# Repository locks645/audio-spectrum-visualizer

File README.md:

# audio-spectrum-visualizer

SDSU Senior Design 2024-2025, Team 14 Audio Spectrum Visualizer

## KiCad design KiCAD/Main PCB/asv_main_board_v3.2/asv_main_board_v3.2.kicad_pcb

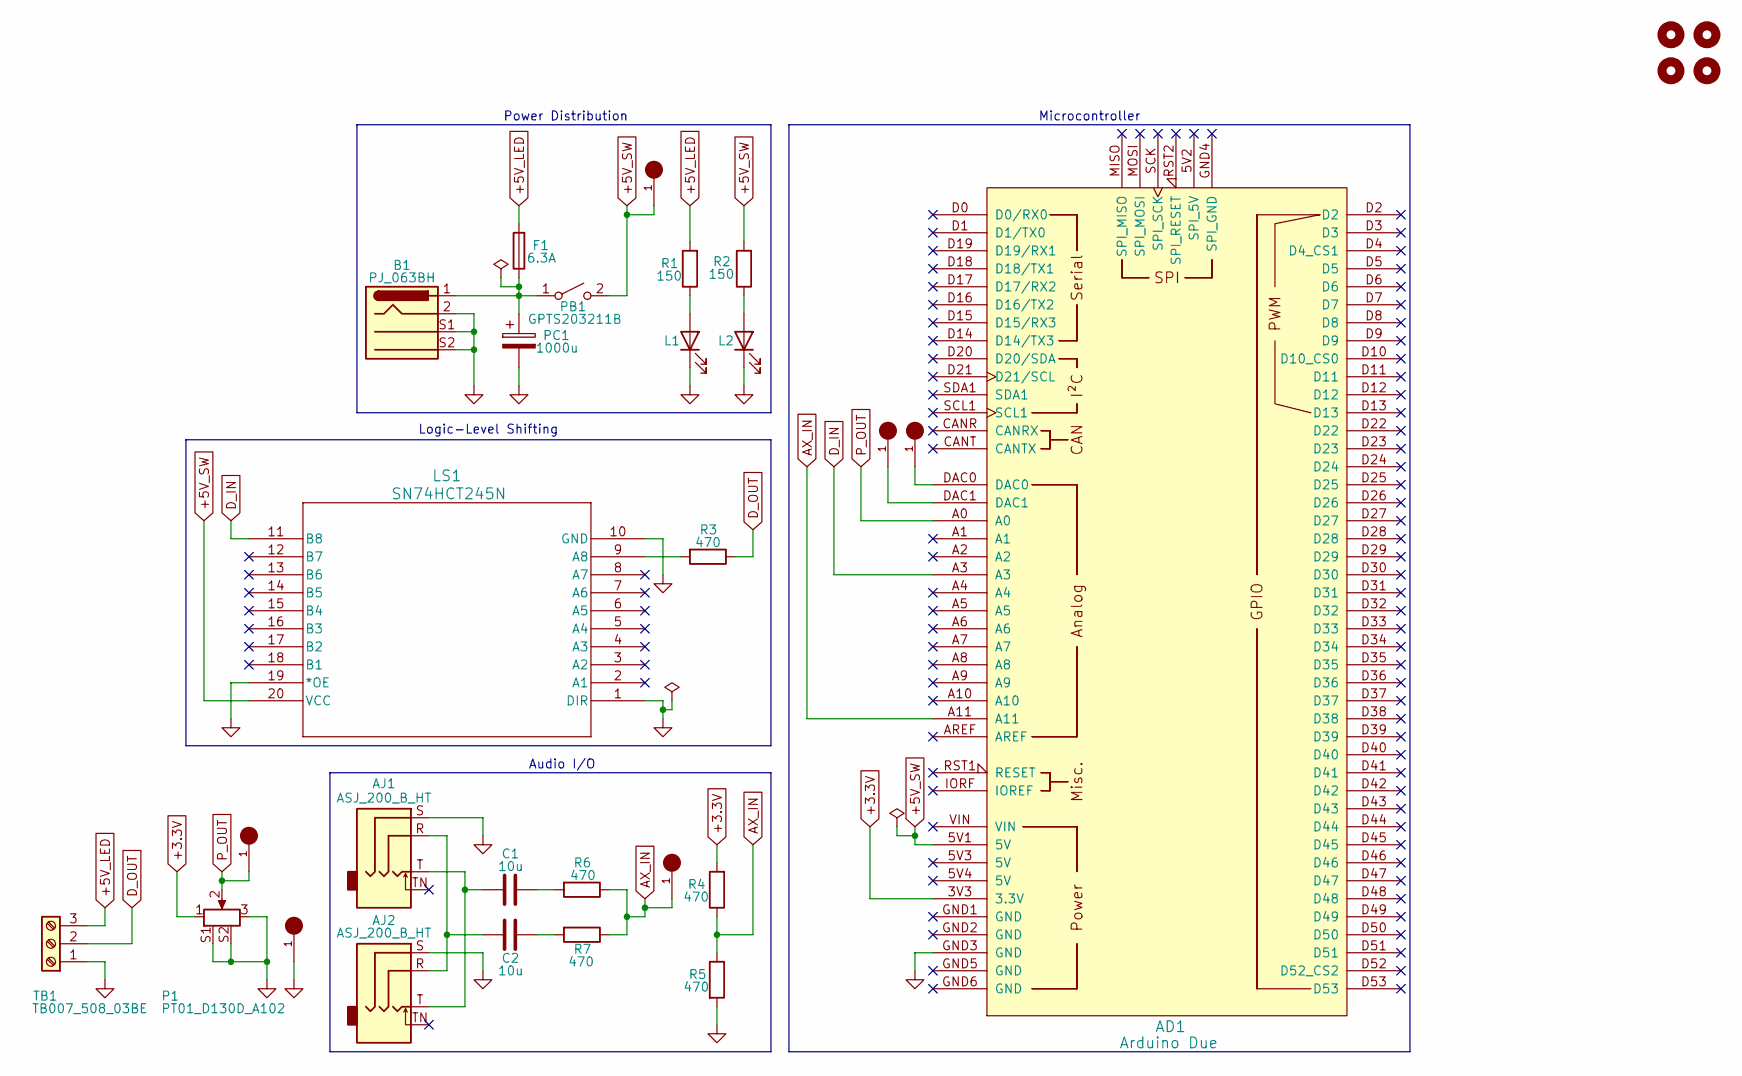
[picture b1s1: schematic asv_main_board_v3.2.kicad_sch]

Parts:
AD1: Arduino Due; Arduino_Due_Shield
AJ1, AJ2: ASJ_200_B_HT; ASJ-200-B-HT_ADM
B1: PJ_063BH; CUI_PJ-063BH
C1, C2: 10u; CAP_C324C_MR_X7R_KEM
F1: 6.3A; FUSE_560_1009_LTF
H1, H2, H3, H4: MountingHole; MountingHole_3.2mm_M3
L1, L2: LED; LED_D3.0mm
LS1: SN74HCT245N; N20
P1: PT01_D130D_A102; TRIM_PT01-D130D-A102
PB1: GPTS203211B; SWITCH_03211B
PC1: 1000u; CAPPRD500W60D800H1150
R1, R2: 150; R_Axial_DIN0207_L6.3mm_D2.5mm_P10.16mm_Horizontal
R3: 470; R_Axial_DIN0207_L6.3mm_D2.5mm_P10.16mm_Horizontal
R4, R5, R6, R7: 470; STA_RSMF2_STP
TB1: TB007_508_03BE; CUI_TB007-508-03BE
TP1, TP2, TP3, TP4, TP5, TP6: 5275; KEYSTONE_5275

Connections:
+3.3V: AD1.3V3 (3.3V), P1.1, R4.2
+5V_LED: F1.2, R1.2, TB1.3
+5V_SW: AD1.5V1 (5V), LS1.20 (VCC), PB1.2 (B), R2.2, TP2.1
AX_IN: AD1.A11, R4.1, R5.1, R6.1, R7.1, TP6.1
D_IN: AD1.A3, LS1.11 (B8)
D_OUT: R3.1, TB1.2
GND: AD1.GND3 (GND), AJ1.S, AJ2.S, B1.2, B1.S1, B1.S2, L1.1 (K), L2.1 (K), LS1.1 (DIR), LS1.10 (GND), LS1.19 (*OE), P1.3, P1.S1, P1.S2, PC1.2, R5.2, TB1.1, TP1.1
unnamed: AD1.DAC0, TP3.1
unnamed: AD1.DAC1, TP4.1
unnamed: AJ1.R, AJ2.R, C2.2
unnamed: AJ1.T, AJ2.T, C1.2
unnamed: C1.1, R6.2
unnamed: C2.1, R7.2
unnamed: L1.2 (A), R1.1
unnamed: L2.2 (A), R2.1
unnamed: LS1.9 (A8), R3.2
unnamed: B1.1, F1.1, PB1.1 (A), PC1.1
P_OUT: AD1.A0, P1.2, TP5.1

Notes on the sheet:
Power Distribution
Audio I/O
Microcontroller
Logic-Level Shifting

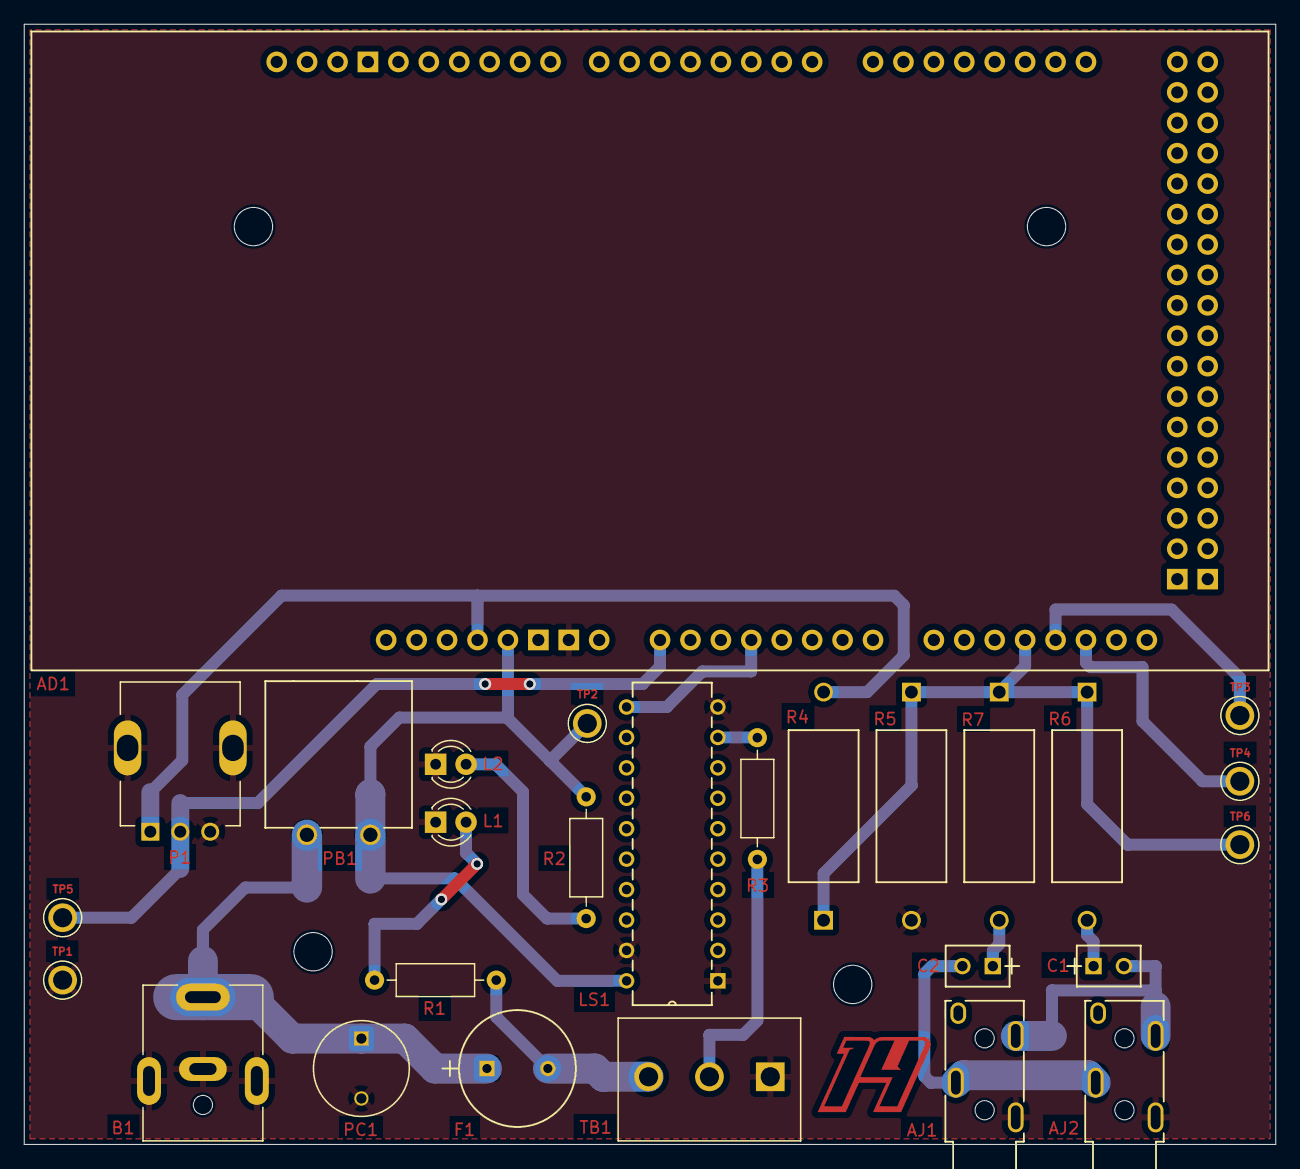
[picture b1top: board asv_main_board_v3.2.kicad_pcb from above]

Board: 2 copper layers, 104.5 x 93.5 mm, 31 parts (0 on the bottom side), 18 nets.

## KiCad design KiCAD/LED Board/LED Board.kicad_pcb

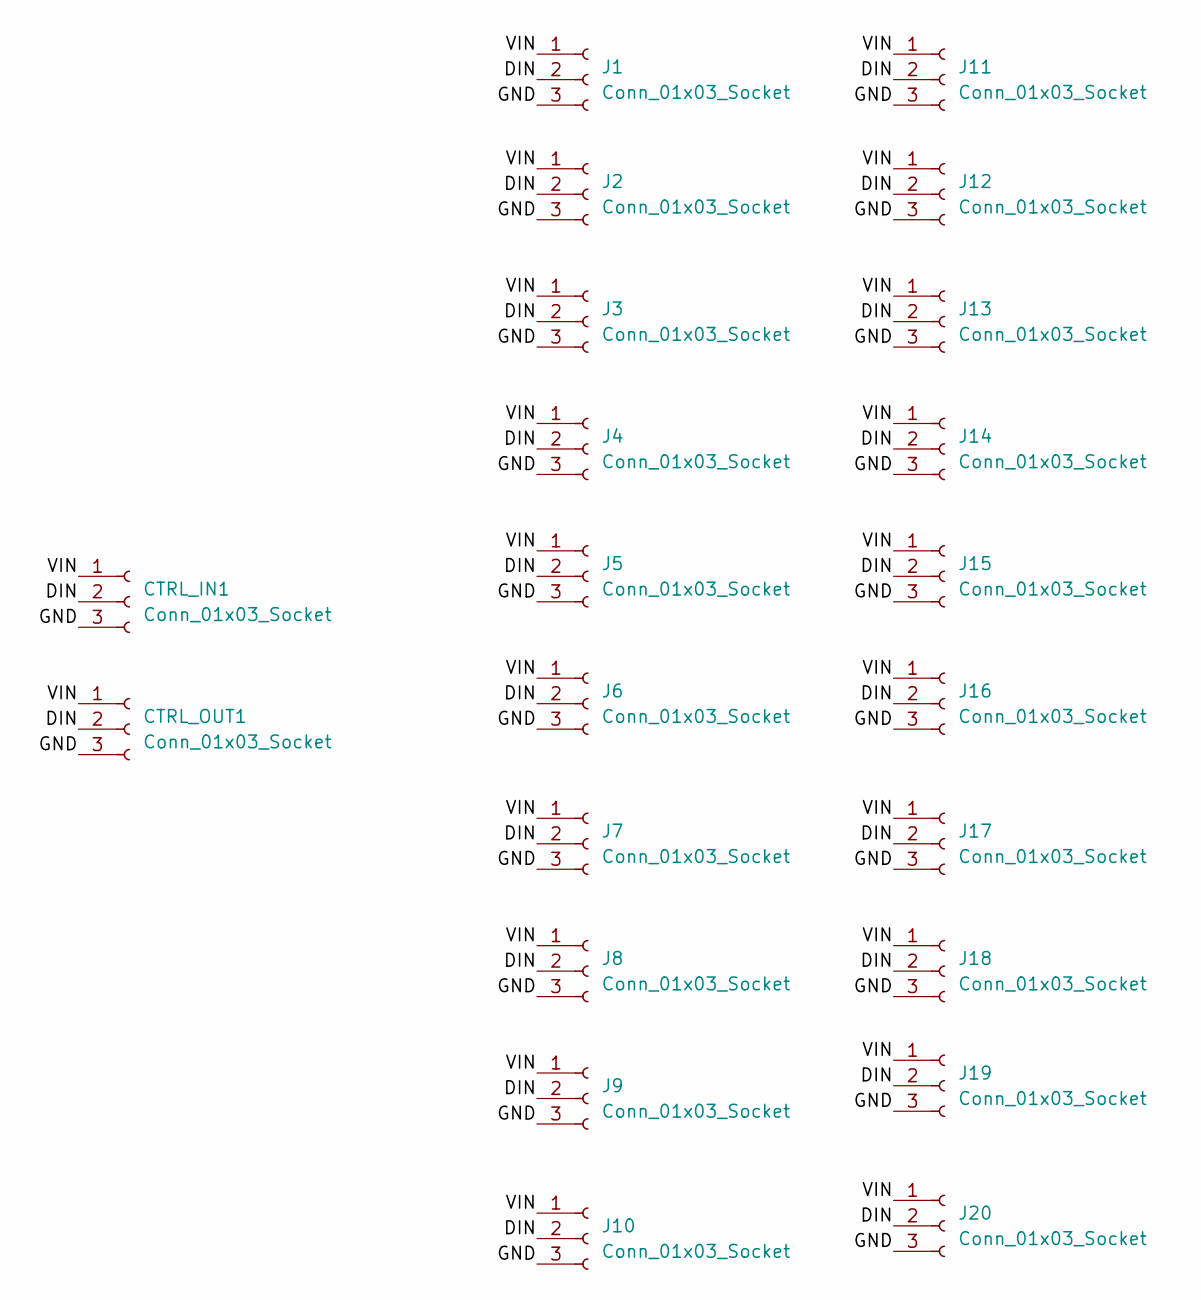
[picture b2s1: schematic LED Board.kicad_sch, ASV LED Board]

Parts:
CTRL_IN1: Conn_01x03_Socket; PinSocket_1x03_P2.54mm_Vertical_HandSolder
CTRL_OUT1: Conn_01x03_Socket; PinSocket_1x03_P2.54mm_Vertical_HandSolder
J1, J2, J3, J4, J5, J6, J7, J8, J9, J10, J11, J12, J13, J14, J15, J16, J17, J18, J19, J20: Conn_01x03_Socket; PinSocket_1x03_P2.54mm_Vertical_HandSolder

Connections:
/DIN: CTRL_IN1.2, CTRL_OUT1.2, J1.2, J2.2, J3.2, J4.2, J5.2, J6.2, J7.2, J8.2, J9.2, J10.2, J11.2, J12.2, J13.2, J14.2, J15.2, J16.2, J17.2, J18.2, J19.2, J20.2
/GND: CTRL_IN1.3, CTRL_OUT1.3, J1.3, J2.3, J3.3, J4.3, J5.3, J6.3, J7.3, J8.3, J9.3, J10.3, J11.3, J12.3, J13.3, J14.3, J15.3, J16.3, J17.3, J18.3, J19.3, J20.3
/VIN: CTRL_IN1.1, CTRL_OUT1.1, J1.1, J2.1, J3.1, J4.1, J5.1, J6.1, J7.1, J8.1, J9.1, J10.1, J11.1, J12.1, J13.1, J14.1, J15.1, J16.1, J17.1, J18.1, J19.1, J20.1

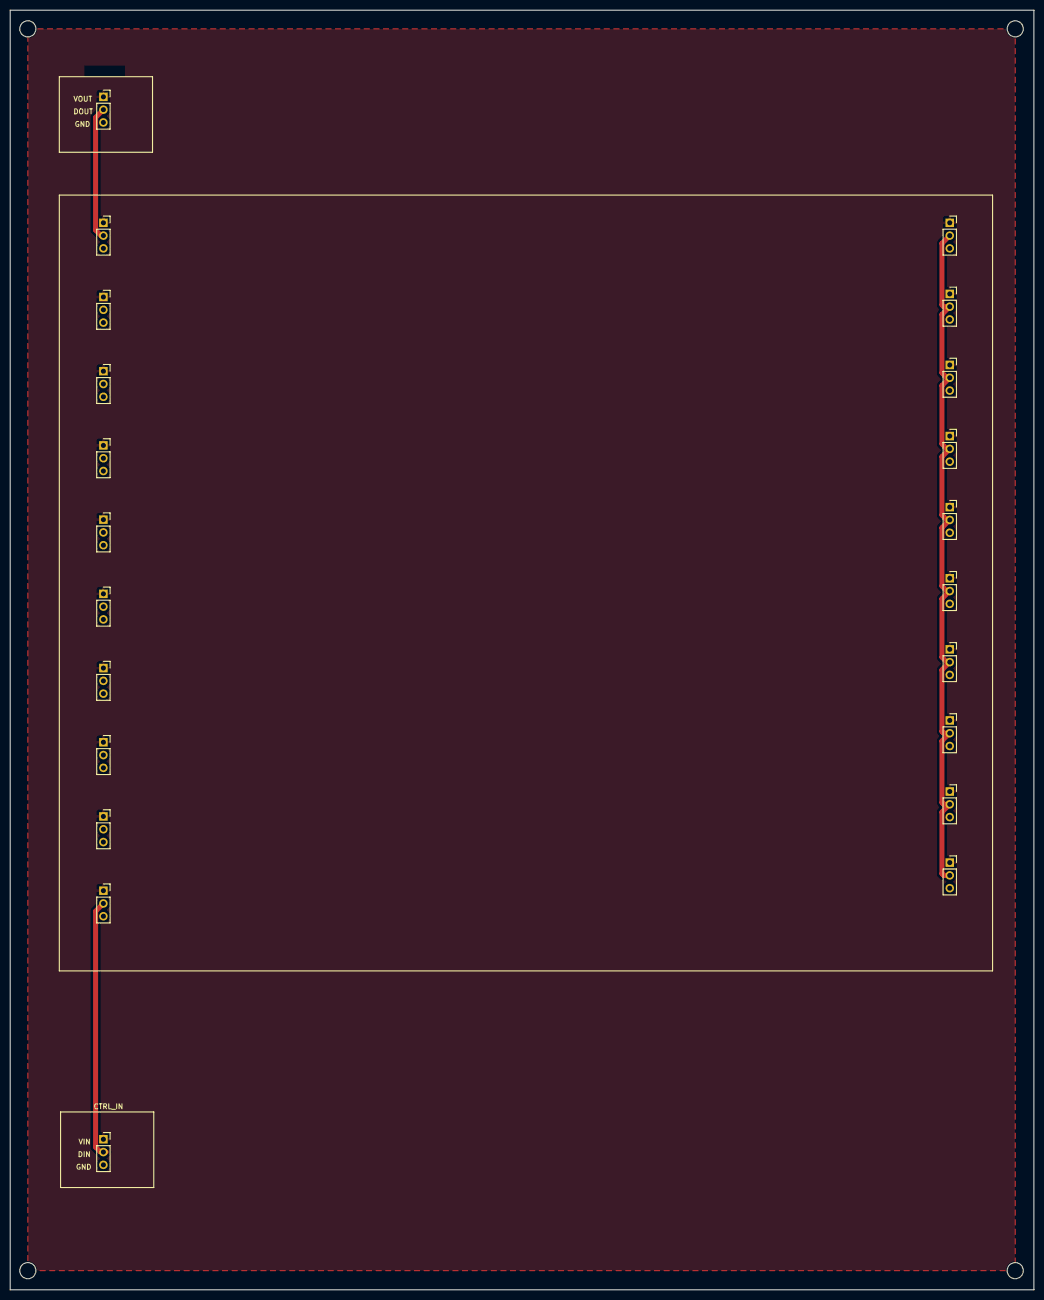
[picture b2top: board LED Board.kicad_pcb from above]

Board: 2 copper layers, 203.2 x 254.0 mm, 22 parts (0 on the bottom side), 3 nets.

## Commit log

2024-11-22 example code
2025-04-04 Create ledSocket
2025-04-04 Create LEDPCB
2025-04-08 Updated LED Socket Board
2025-05-06 commit final code
2025-05-09 Current printed PCB added
